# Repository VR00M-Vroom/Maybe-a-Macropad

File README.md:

# Maybe-a-Macropad
Its a exposed macropad

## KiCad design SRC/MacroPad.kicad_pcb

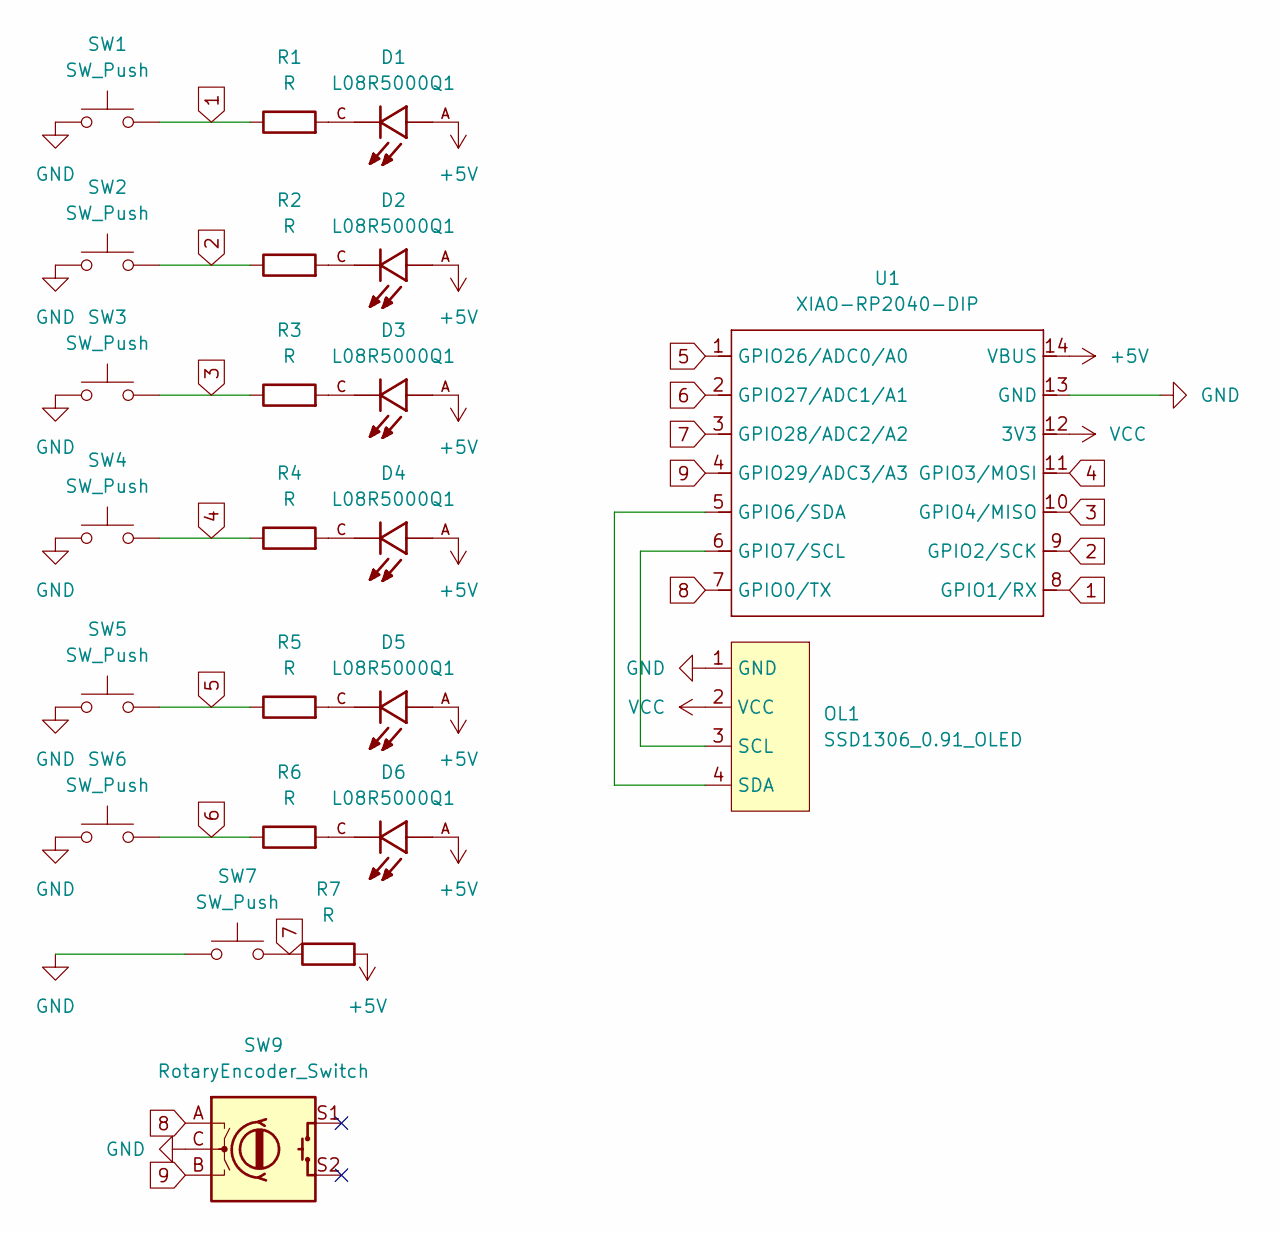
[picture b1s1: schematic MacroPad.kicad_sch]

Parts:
D1, D2, D3, D4, D5, D6: L08R5000Q1; LEDRD254W57D500H1070; PARTREV NA
OL1: SSD1306_0.91_OLED; SSD1306-0.91-OLED-4pin-128x32
R1, R2, R3, R4, R5, R6, R7: R; R_Axial_DIN0204_L3.6mm_D1.6mm_P5.08mm_Horizontal
SW1, SW2, SW3, SW4, SW5, SW6, SW7: SW_Push; SW_Cherry_MX_1.00u_PCB
SW9: RotaryEncoder_Switch; RotaryEncoder_Alps_EC11E-Switch_Vertical_H20mm
U1: XIAO-RP2040-DIP

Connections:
1: R1.1, SW1.2, U1.8 (GPIO1/RX)
2: R2.1, SW2.2, U1.9 (GPIO2/SCK)
3: R3.1, SW3.2, U1.10 (GPIO4/MISO)
4: R4.1, SW4.2, U1.11 (GPIO3/MOSI)
5: R5.1, SW5.2, U1.1 (GPIO26/ADC0/A0)
6: R6.1, SW6.2, U1.2 (GPIO27/ADC1/A1)
7: R7.1, SW7.2, U1.3 (GPIO28/ADC2/A2)
8: SW9.A, U1.7 (GPIO0/TX)
9: SW9.B, U1.4 (GPIO29/ADC3/A3)
+5V: D1.A, D2.A, D3.A, D4.A, D5.A, D6.A, R7.2, U1.14 (VBUS)
GND: OL1.1 (GND), SW1.1, SW2.1, SW3.1, SW4.1, SW5.1, SW6.1, SW7.1, SW9.C, U1.13 (GND)
unnamed: D1.C, R1.2
unnamed: D2.C, R2.2
unnamed: D3.C, R3.2
unnamed: D4.C, R4.2
unnamed: D5.C, R5.2
unnamed: D6.C, R6.2
unnamed: OL1.3 (SCL), U1.6 (GPIO7/SCL)
unnamed: OL1.4 (SDA), U1.5 (GPIO6/SDA)
VCC: OL1.2 (VCC), U1.12 (3V3)

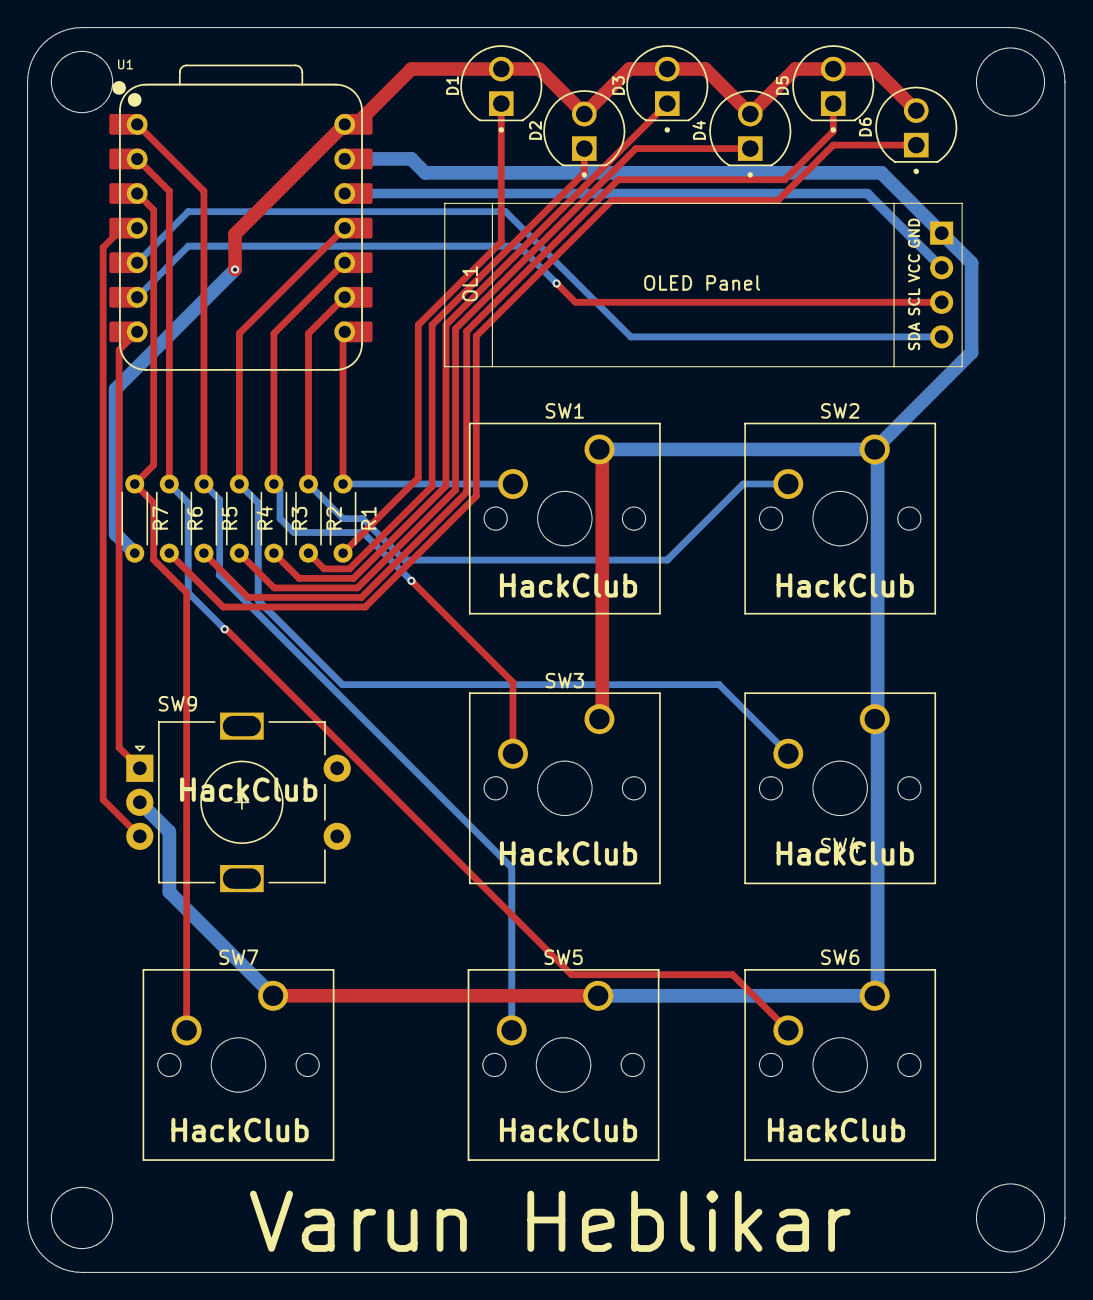
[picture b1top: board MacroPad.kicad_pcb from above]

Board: 2 copper layers, 76.2 x 91.4 mm, 23 parts (0 on the bottom side), 20 nets.

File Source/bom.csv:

Designator,Footprint,Quantity,Value,LCSC Part #
OL1,SSD1306-0.91-OLED-4pin-128x32,1,SSD1306_0.91_OLED,
"SW1, SW2, SW3, SW4, SW5, SW6, SW7",SW_Cherry_MX_1.00u_PCB,7,SW_Push,
SW9,RotaryEncoder_Alps_EC11E-Switch_Vertical_H20mm,1,RotaryEncoder_Switch,
U1,XIAO-RP2040-DIP,1,XIAO-RP2040-DIP,

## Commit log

2025-08-17 Create File
2025-08-17 Create Filler
